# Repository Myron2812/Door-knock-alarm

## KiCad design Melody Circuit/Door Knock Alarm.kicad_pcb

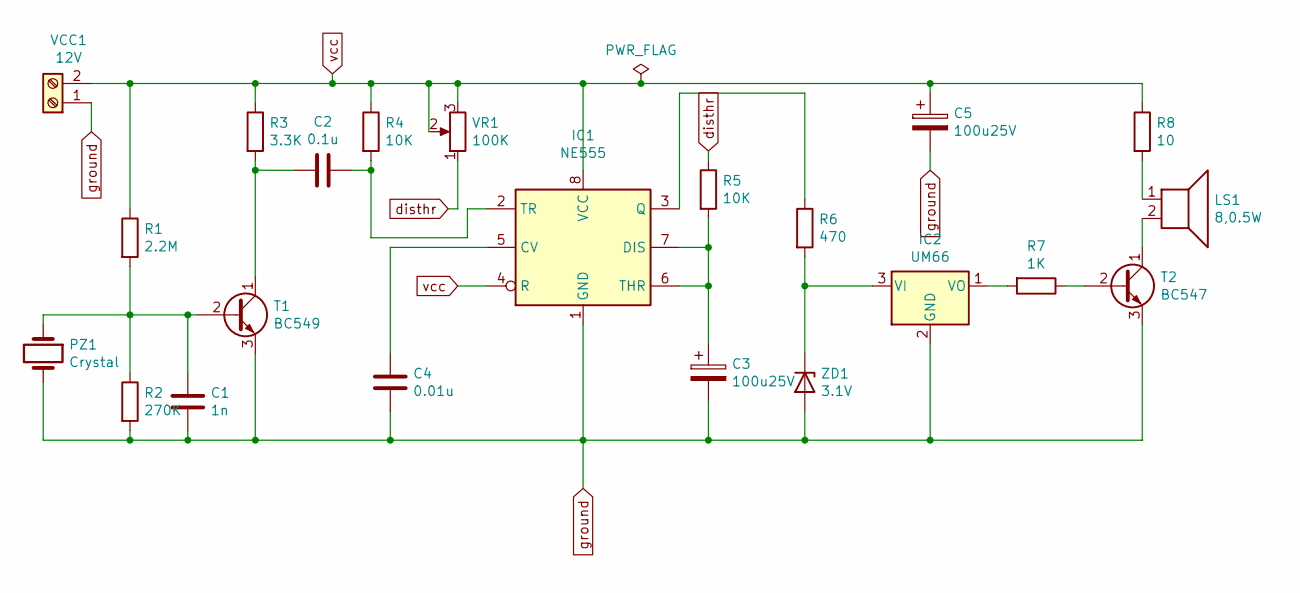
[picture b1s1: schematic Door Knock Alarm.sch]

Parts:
C1: 1n; C_Disc_D9.0mm_W5.0mm_P10.00mm
C2: 0.1u; C_Disc_D7.5mm_W5.0mm_P10.00mm
C3, C5: 100u25V; CP_Axial_L10.0mm_D4.5mm_P15.00mm_Horizontal
C4: 0.01u; C_Disc_D7.5mm_W5.0mm_P10.00mm
IC1: NE555; DIP-8_W7.62mm
IC2: UM66; TO-92_Inline
LS1: 8,0.5W; PinHeader_2x01_P1.00mm_Vertical
PZ1: Crystal; Crystal_AT310_D3.0mm_L10.0mm_Horizontal
R1: 2.2M; R_Axial_DIN0207_L6.3mm_D2.5mm_P10.16mm_Horizontal
R2: 270K; R_Axial_DIN0207_L6.3mm_D2.5mm_P10.16mm_Horizontal
R3: 3.3K; R_Axial_DIN0207_L6.3mm_D2.5mm_P10.16mm_Horizontal
R4, R5: 10K; R_Axial_DIN0207_L6.3mm_D2.5mm_P10.16mm_Horizontal
R6: 470; R_Axial_DIN0207_L6.3mm_D2.5mm_P10.16mm_Horizontal
R7: 1K; R_Axial_DIN0207_L6.3mm_D2.5mm_P10.16mm_Horizontal
R8: 10; R_Axial_DIN0207_L6.3mm_D2.5mm_P10.16mm_Horizontal
T1: BC549; TO-92_Inline
T2: BC547; TO-92_Inline
VCC1: 12V; PinHeader_2x01_P1.00mm_Vertical
VR1: 100K; Potentiometer_Vishay_TS53YJ_Vertical
ZD1: 3.1V; D_DO-35_SOD27_P7.62mm_Horizontal

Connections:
unnamed: C1.1, PZ1.1, R1.2, R2.1, T1.2 (B)
unnamed: C2.1, IC1.2 (TR), R4.2
unnamed: C2.2, R3.2, T1.1 (C)
unnamed: C3.1, IC1.6 (THR), IC1.7 (DIS), R5.2
unnamed: C4.1, IC1.5 (CV)
unnamed: IC1.3 (Q), R6.1
unnamed: IC2.1 (VO), R7.2
unnamed: IC2.3 (VI), R6.2, ZD1.1 (K)
unnamed: LS1.1, R8.2
unnamed: LS1.2, T2.1 (C)
unnamed: R7.1, T2.2 (B)
disthr: R5.1, VR1.1
ground: C1.2, C3.2, C4.2, C5.2, IC1.1 (GND), IC2.2 (GND), PZ1.2, R2.2, T1.3 (E), T2.3 (E), VCC1.1, ZD1.2 (A)
vcc: C5.1, IC1.4 (R), IC1.8 (VCC), R1.1, R3.1, R4.1, R8.1, VCC1.2, VR1.2, VR1.3

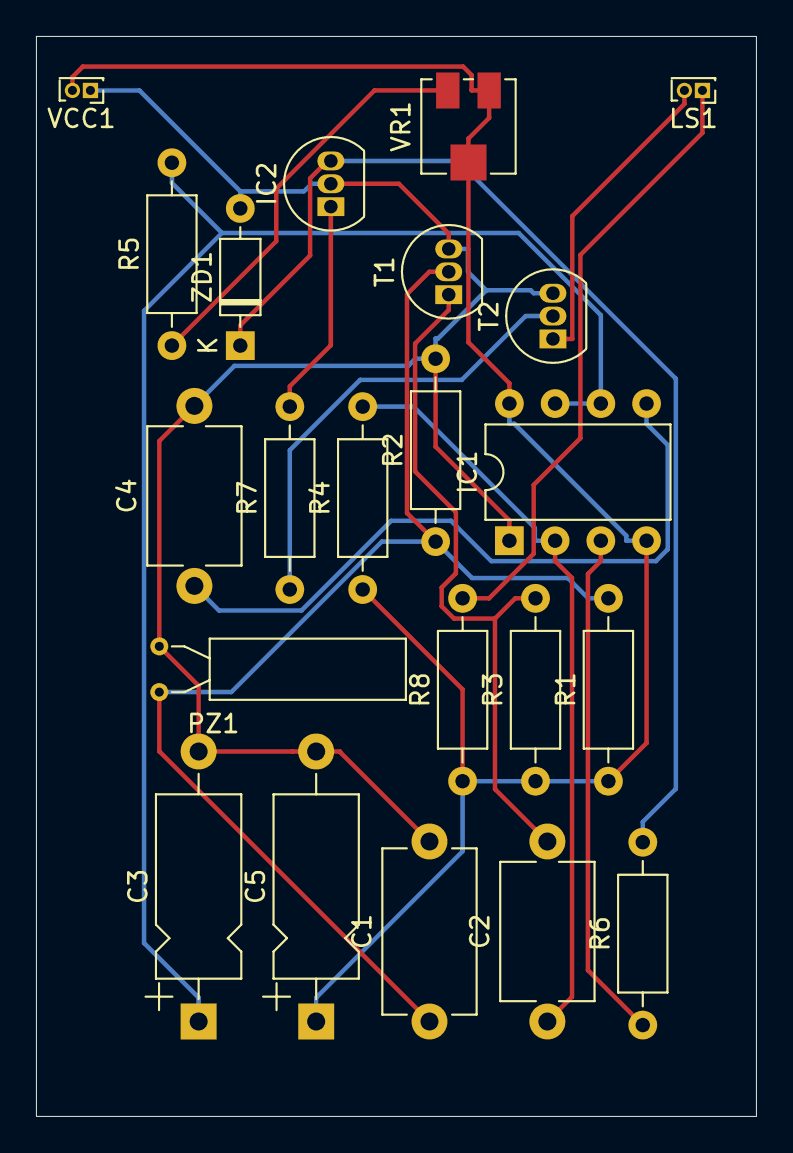
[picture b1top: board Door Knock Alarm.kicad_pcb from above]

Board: 2 copper layers, 40.0 x 60.0 mm, 22 parts (0 on the bottom side), 14 nets.

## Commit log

2023-02-14 First commit
    First commit
